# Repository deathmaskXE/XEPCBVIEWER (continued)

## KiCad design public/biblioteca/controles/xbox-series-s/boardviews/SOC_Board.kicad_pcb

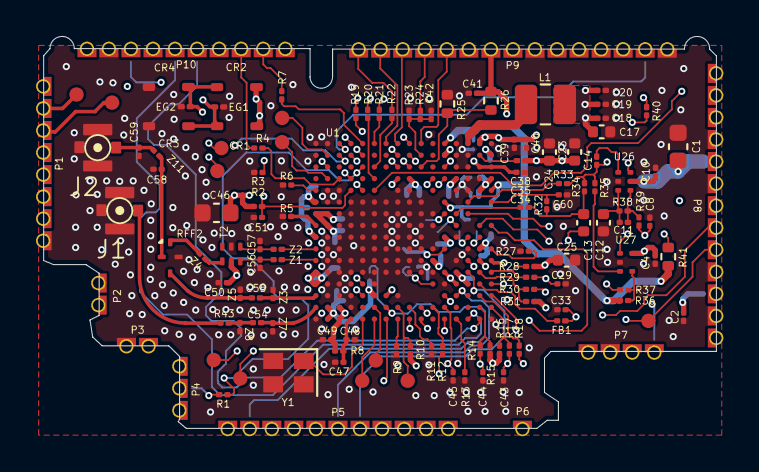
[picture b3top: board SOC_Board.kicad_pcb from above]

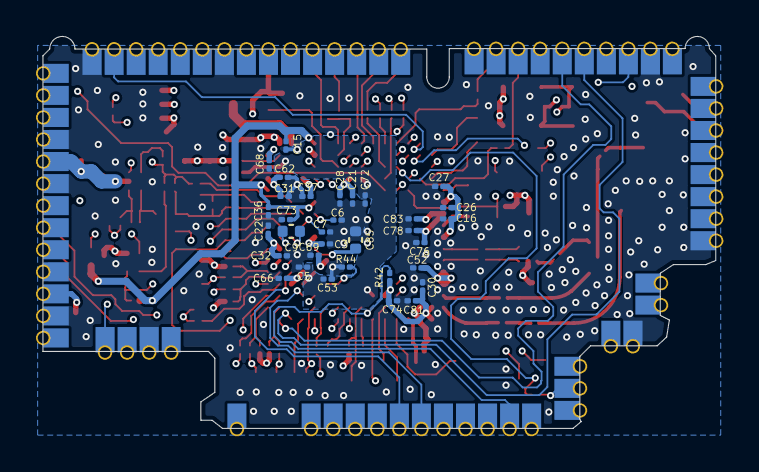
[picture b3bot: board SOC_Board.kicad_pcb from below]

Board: 4 copper layers, 37.4 x 21.8 mm, 162 parts (33 on the bottom side), 125 nets.

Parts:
C1, C46: C; C_0603_1608Metric
C2, C3, C4, C5, C6, C8, C10, C11, C14, C15, C16, C18, C19, C20, C21, C22, C26, C27, C28, C29, C30, C31, C32, C33, C34, C35, C36, C37, C38, C39, C40, C41, C42, C43, C44, C45, C47, C48, C49, C50, C51, C52, C53, C54, C55, C56, C57, C58, C59, C60, C62, C66, C68, C69, C72, C73, C74, C76, C78, C81, C83: C; Xbox_C_01005_0402Metric
C7: DNI; Xbox_C_01005_0402Metric
C9, C12, C13, C17, C23, C24, C25, C85: C; C_0402_1005Metric
CR1, CR2, CR3, CR4: E1; Xbox_Diode
EG1, EG2: D; D_01005_0402Metric
FB1: FerriteBead; Xbox_R_01005_0402Metric
J1, J2: Conn_Coaxial; Xbox_CoaxConnector
L1: 2uH; L_1008_2520Metric
P1: 1-8; Castellated_Holes_1_8
P2: 9-10; Castellated_Holes_9-10
P3: 11-12; Castellated_Holes_11_12
P4: 13-15; Castellated_Holes_13-15
P5: 16-26; Castellated_Holes_16-26
P6: 27; Castellated_Holes_27
P7: 28-31; Castellated_Holes_28-31
P8: 32_44; Castellated_Holes_32-44
P9: 59-45; Castellated_Holes_45-59
P10: 69-60; Castellated_Holes_60-69
R1, R4, R14, R17, R18, R20, R22, R29, R30, R40: 33; Xbox_R_01005_0402Metric
R2: 139k; Xbox_R_01005_0402Metric
R3, R10, R11, R13, R35, R37, R38: 10k; Xbox_R_01005_0402Metric
R5, R7, R12, R19, R21: 51; Xbox_R_01005_0402Metric
R6, R33, R43, R44: 0; Xbox_R_01005_0402Metric
R8: 20; Xbox_R_01005_0402Metric
R9, R42: 4.7k; Xbox_R_01005_0402Metric
R15, R16: 2k; Xbox_R_01005_0402Metric
R23: 33k; Xbox_R_01005_0402Metric
R24: 30k; Xbox_R_01005_0402Metric
R25: 157k; R_0402_1005Metric
R26: 46k; R_0402_1005Metric
R27: 5.1k; Xbox_R_01005_0402Metric
R28, R31: 2.2k; Xbox_R_01005_0402Metric
R32: 1k; Xbox_R_01005_0402Metric
R34: 1.5k; Xbox_R_01005_0402Metric
R36: 100k; Xbox_R_01005_0402Metric
R39: 402; Xbox_R_01005_0402Metric
R41: 330k; R_0402_1005Metric
RFF2: Xbox_RF_Filter
T2: Balun_Johanson_1.6x0.8mm
TP1, TP2, TP3, TP4, TP5, TP6, TP15, TP16, TP20, TP21, TP77, TP78: TestPoint; Xbox_TestPoint_0.8mm
U1: Xbox_ARM_BGA_Layout16x16
U26: SOT-886
U27: NCX2202; SOT-886
Y1: 26MHz; Oscillator_SMD_SeikoEpson_SG210-4Pin_2.5x2.0mm
Z1, Z2, Z3, Z4, Z5, Z7, Z8, Z11: Xbox_R_01005_0402Metric

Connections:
3V_B+: P9.12, R24.2
+1V8: C37.1, C41.1, P9.9, R26.2, U1.N13 (Vref)
+3.3V: C1.1, C2.1, C4.1, C10.1, C16.1, C21.1, C22.1, C23.1, C24.1, C25.1, C26.1, C27.1, C28.1, C30.1, C31.1, C32.1, C38.1, C39.1, C40.1, C46.1, C50.1, C52.1, C62.1, C66.1, C69.1, C74.1, C81.1, CR1.1 (K), CR2.1 (K), P8.3, P8.9, P9.8, R2.1, R10.1, R15.1, R16.1, R28.1, R31.1, R42.1, T2.2, U1.A4 (4), U1.A5 (5), U1.A8 (8), U1.A11 (11), U1.B1 (17), U1.B2 (18), U1.F3 (83), U1.J13 (141), U1.L6 (166), U1.N5 (197), U1.P4 (212), U1.R7 (231), U1.R12 (236), U1.R16 (240), U1.T13 (253), U26.5 (VCC), U27.5 (V+)
/SOC_Board/1: P1.1, U1.H15 (127)
/SOC_Board/4: P1.4, U1.C15 (47)
/SOC_Board/5: P1.5, U1.P6 (214)
/SOC_Board/6: C29.1, P1.6, R29.1
/SOC_Board/7: P1.7, R30.1
/SOC_Board/9: P2.1, U1.T4 (244)
/SOC_Board/10: P2.2, U1.J1 (129)
/SOC_Board/12: P3.2, U1.K1 (145)
/SOC_Board/13: P4.1, U1.J15 (143)
/SOC_Board/14: P4.2, R1.2
/SOC_Board/15: P4.3, U1.L13 (173)
/SOC_Board/16: P5.1, U1.T9 (SPKR-R)
/SOC_Board/17: P5.2, R42.2, U1.G2 (98)
/SOC_Board/18: P5.3, R12.1
/SOC_Board/19: P5.4, U1.M1 (177)
/SOC_Board/20: C45.1, P5.5, U1.M2 (178)
/SOC_Board/21: P5.6, U1.N3 (195)
/SOC_Board/22: P5.7, U1.P5 (213)
/SOC_Board/23: C44.1, P5.8, R14.1
/SOC_Board/24: C43.1, P5.9, R17.1
/SOC_Board/25: P5.10, R18.1
/SOC_Board/26: P5.11, U1.T3 (243)
/SOC_Board/27: C33.1, FB1.2, P6.1
/SOC_Board/28: P7.1, R37.2, U1.D15 (63)
/SOC_Board/30: P7.3, U1.M14 (190)
/SOC_Board/31: C14.1, P7.4, R33.2, R34.2, R35.2
/SOC_Board/32: P8.1, U1.R9 (SPKR-L)
/SOC_Board/36: P8.5, TP78.1, U1.G1 (97)
/SOC_Board/37: P8.6, U1.K2 (146)
/SOC_Board/38: P8.7, R41.1
/SOC_Board/43: C51.1, P8.12, P10.4, R2.2, U1.D12 (60)
/SOC_Board/44: P8.13, U1.F12 (92)
/SOC_Board/46: P9.2, U1.C16 (48)
/SOC_Board/47: P9.3, R40.2
/SOC_Board/48: P9.4, R21.2
/SOC_Board/49: P9.5, R20.2
/SOC_Board/50: P9.6, R19.2
/SOC_Board/54: P9.10, U1.J14 (142)
/SOC_Board/55: P9.11, U1.K16 (160)
/SOC_Board/57: P9.13, U1.H16 (128)
/SOC_Board/58: P9.14, U1.G16 (112)
/SOC_Board/59: P9.15, R22.2
/SOC_Board/60: P10.1, U1.J16 (144)
/SOC_Board/61: P10.2, R7.1
/SOC_Board/62: P10.3, R4.1
/SOC_Board/64: P10.5, U1.R1 (225)
/SOC_Board/65: P10.6, U1.P1 (209)
/SOC_Board/66: P10.7, U1.H14 (126)
/SOC_Board/67: P10.8, U1.M13 (189)
/SOC_Board/69: P10.10, U1.D16 (64)
D+: CR1.2 (A), CR3.1 (K), EG1.1 (K), P1.2, TP2.1, U1.R6 (DP)
D-: CR2.2 (A), CR4.1 (K), EG2.1 (K), P1.3, TP1.1, U1.T6 (DM)
GND: C1.2, C2.2, C3.2, C4.2, C5.2, C6.2, C7.1, C8.2, C10.2, C12.1, C15.2, C16.2, C17.2, C18.2, C19.2, C20.2, C21.2, C22.2, C23.2, C24.2, C25.2, C26.2, C27.2, C28.2, C29.2, C30.2, C31.2, C32.2, C33.2, C35.2, C36.2, C37.2, C39.2, C40.2, C41.2, C42.1, C43.2, C44.2, C45.2, C46.2, C47.2, C48.1, C49.2, C50.2, C51.2, C52.2, C53.2, C56.2, C57.2, C58.2, C59.2, C60.2, C62.2, C66.2, C68.2, C69.2, C72.2, C73.2, C74.2, C76.2, C78.2, C81.2, C83.2, C85.2, CR3.2 (A), CR4.2 (A), EG1.2 (A), EG2.2 (A), J1.2 (Ext), J2.2 (Ext), P1.8, P3.1, P7.2, P8.2, P8.4, P8.8, P8.10, P9.1, P9.7, P10.9, R3.2, R5.2, R6.2, R9.2, R11.2, R13.2, R23.1, R25.2, R27.2, R44.2, RFF2.4, T2.5, U1.A1 (1), U1.A15 (15), U1.A16 (16), U1.B3 (19), U1.B4 (20), U1.B5 (21), U1.B6 (22), U1.B7 (23), U1.B8 (24), U1.B11 (27), U1.B12 (28), U1.B16 (32), U1.C3 (35), U1.C4 (36), U1.C5 (37), U1.C6 (38), U1.C7 (39), U1.C8 (40), U1.C9 (41), U1.C10 (42), U1.C11 (43), U1.C12 (44), U1.D2 (50), U1.D3 (51), U1.D4 (52), U1.D5 (53), U1.D6 (54), U1.D8 (56), U1.D9 (57), U1.D10 (58), U1.D11 (59), U1.E5 (69), U1.E6 (70), U1.E7 (71), U1.E8 (72), U1.E9 (736), U1.E10 (74), U1.E11 (75), U1.F4 (84), U1.F5 (85), U1.F6 (86), U1.F7 (87), U1.F8 (88), U1.F9 (89), U1.F10 (90), U1.F11 (91), U1.G5 (101), U1.G6 (102), U1.G7 (103), U1.G8 (104), U1.G9 (105), U1.G10 (106), U1.G11 (107), U1.H3 (115), U1.H5 (117), U1.H6 (118), U1.H7 (119), U1.H8 (120), U1.H9 (121), U1.H10 (122), U1.H11 (123), U1.H12 (124), U1.J5 (133), U1.J6 (134), U1.J7 (135), U1.J8 (136), U1.J9 (137), U1.J10 (138), U1.J11 (139), U1.J12 (140), U1.K5 (149), U1.K6 (150), U1.K7 (151), U1.K8 (152), U1.K9 (153), U1.K10 (154), U1.K11 (155), U1.L5 (165), U1.L7 (167), U1.L9 (169), U1.L10 (170), U1.M4 (180), U1.N6 (198), U1.N8 (200), U1.N12 (204), U1.N14 (206), U1.N15 (207), U1.N16 (208), U1.P7 (215), U1.P12 (220), U1.P13 (221), U1.P14 (222), U1.P15 (223), U1.R13 (237), U1.T1 (241), U1.T16 (256), U26.2 (GND), U27.2 (V-), Y1.2, Y1.3, Y1.4, Z3.2, Z5.2, Z7.2, Z8.2
GNDA: C7.2, C13.2, P8.11, U1.N9 (201)
unnamed: C13.1, C34.2, R32.2, R34.1
unnamed: C54.1, R43.2, Z8.1
unnamed: C54.2, U1.A2 (RF), Z7.1
unnamed: C55.1, RFF2.3, Z5.1
unnamed: C55.2, U1.A3 (RF), Z3.1
unnamed: C56.1, T2.3, Z1.1
unnamed: C57.1, T2.4, Z2.1
unnamed: C58.1, RFF2.2, Z11.2
unnamed: J1.1 (In), R43.1
unnamed: C59.1, J2.1 (In), Z11.1
unnamed: RFF2.1, Z4.1
unnamed: T2.1, Z4.2
unnamed: R5.1, U1.A9 (9)
unnamed: R6.1, U1.A12 (12)
unnamed: TP5.1, U1.B13 (29)
unnamed: TP4.1, U1.B14 (30)
unnamed: TP77.1, U1.B15 (31)
unnamed: R4.2, U1.C13 (45)
unnamed: C47.1, C48.2, R8.2, U1.D1 (49)
unnamed: R40.1, U1.D13 (61)
unnamed: TP21.1, U1.E3 (67)
unnamed: TP6.1, U1.E4 (68)
unnamed: R3.1, TP3.1, U1.E12 (76)
unnamed: R1.1, U1.E14 (78)
unnamed: R19.1, U1.E15 (79)
unnamed: R7.2, U1.E16 (80)
unnamed: TP15.1, U1.F1 (81)
unnamed: TP16.1, U1.F2 (82)
unnamed: R20.1, U1.F13 (93)
unnamed: R22.1, U1.F14 (94)
unnamed: R21.1, U1.F16 (96)
unnamed: R9.1, U1.H1 (113)
unnamed: R10.2, TP20.1, U1.H2 (114)
unnamed: C5.1, C35.1, C53.1, C72.1, U1.G3 (99), U1.H13 (125), U1.M5 (181), U1.N4 (196), U1.R14 (238), U1.T14 (254)
unnamed: R11.1, U1.J2 (130)
unnamed: R25.1, R26.1, U1.K14 (158)
unnamed: C42.2, R23.2, R24.1, U1.K15 (159)
unnamed: R12.2, U1.L2 (162)
unnamed: R44.1, U1.L4 (164)
unnamed: U1.M3 (179), U26.6 (S), U27.4
unnamed: C85.1, U1.M7 (183)
unnamed: C6.1, U1.M10 (186)
unnamed: C15.1, C36.1, C73.1, R36.1, R41.2, U1.M11 (187), U1.M16 (192), U1.T12 (252)
unnamed: R13.1, U1.N1 (193)
unnamed: C34.1, U1.N10 (202)
unnamed: C9.2, U1.P8 (216)
unnamed: C8.1, R39.2, U1.P10 (218)
unnamed: R33.1, U1.P11 (219)
unnamed: L1.2, U1.P16 (224)
unnamed: R18.2, U1.R3 (227)
unnamed: FB1.1, U1.R4 (228)
unnamed: C9.1, U1.R8 (232)
unnamed: C38.2, U1.R15 (239)
unnamed: R27.1, U1.T7 (247)
unnamed: C60.1, R32.1, U1.T11 (251)
unnamed: U1.E1 (OSC), Y1.1
unnamed: U1.A6 (RF), Z1.2
unnamed: U1.A7 (RF), Z2.2
unnamed: R16.2, R17.2, U1.T2 (SCL2)
unnamed: R30.2, R31.2, U1.R5 (SCL)
unnamed: R14.2, R15.2, U1.R2 (SDA2)
unnamed: R28.2, R29.2, U1.T5 (SDA)
unnamed: C11.2, R38.2, R39.1, U26.4 (X)
unnamed: C11.1, C12.2, R38.1, U26.3 (Y0)
unnamed: C14.2, U26.1 (Y1)
unnamed: R35.1, U27.3 (+)
unnamed: R36.2, R37.1, U27.1 (-)
VCORE: C3.1, C17.1, C18.1, C19.1, C20.1, C49.1, C68.1, C76.1, C78.1, C83.1, L1.1, R8.1, U1.A10 (10), U1.B9 (25), U1.B10 (26), U1.C1 (33), U1.C2 (34), U1.M8 (184), U1.M15 (191), U1.T15 (255)
